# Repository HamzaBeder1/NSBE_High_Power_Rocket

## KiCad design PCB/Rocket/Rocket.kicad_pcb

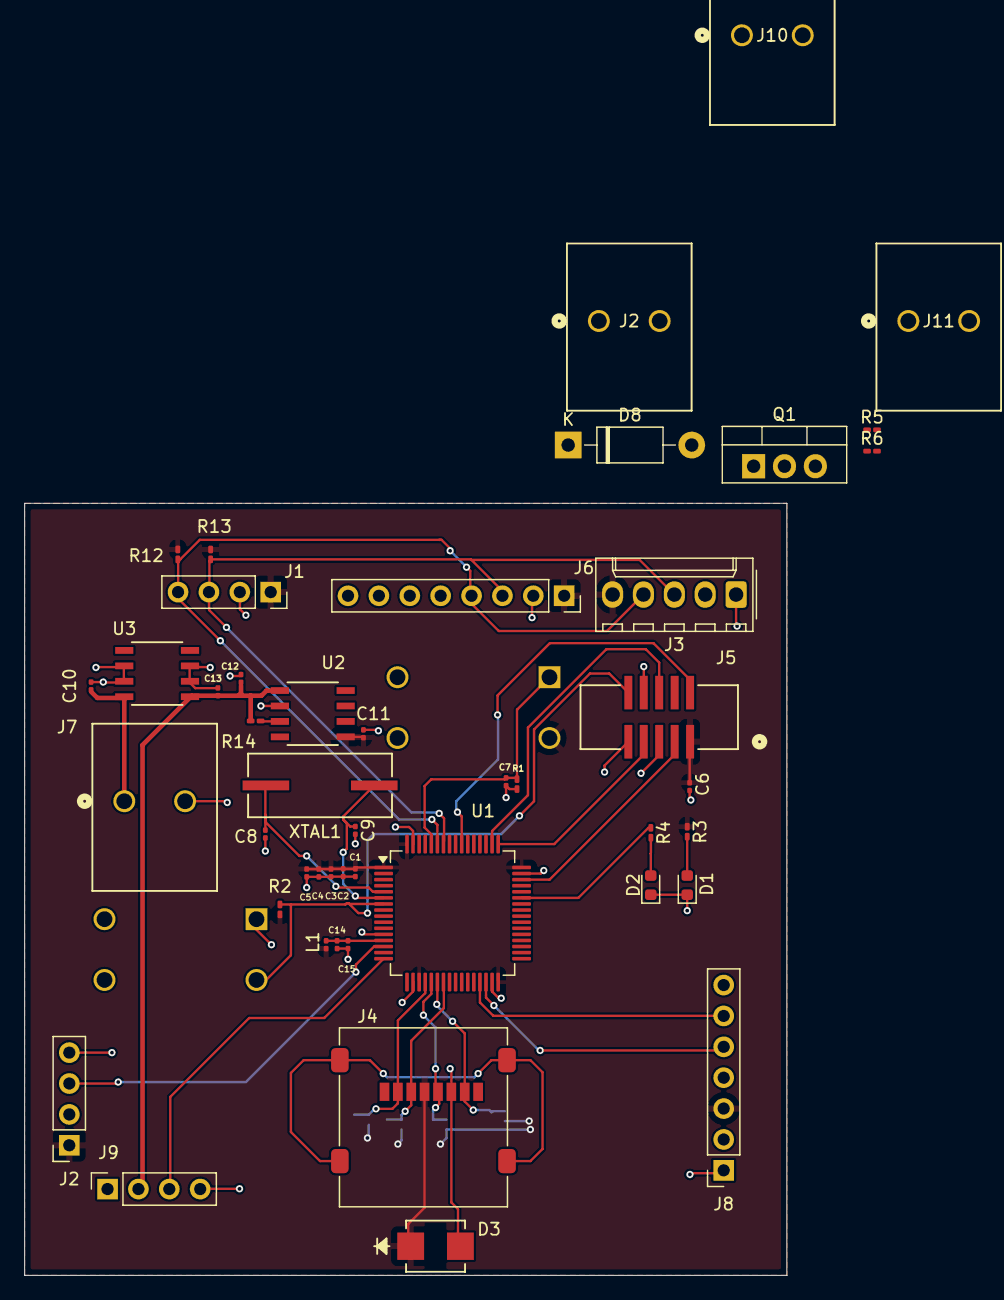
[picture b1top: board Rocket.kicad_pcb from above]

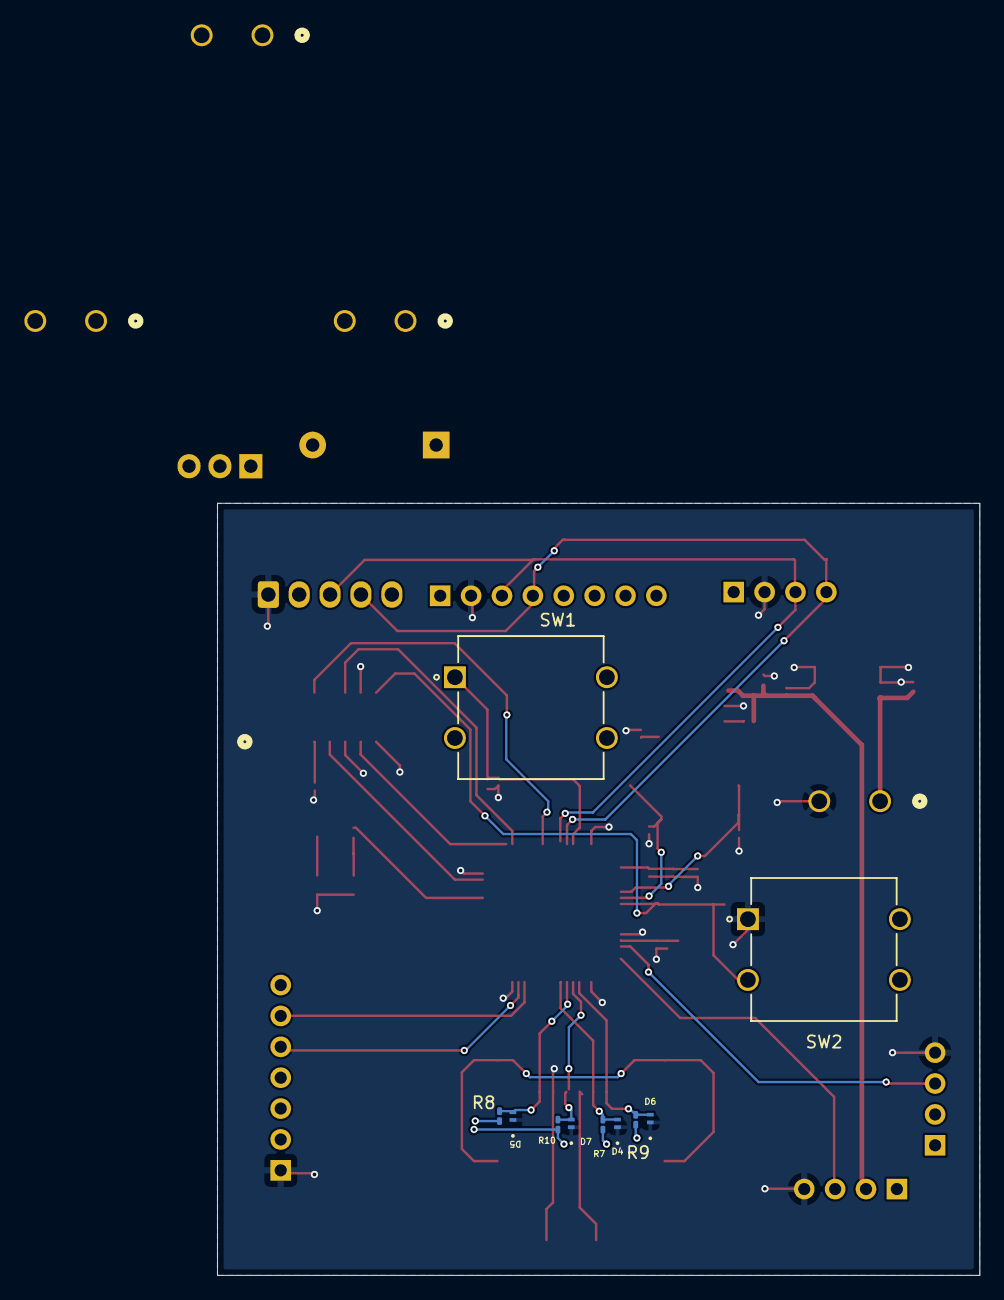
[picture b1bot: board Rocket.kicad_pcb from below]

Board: 2 copper layers, 62.7 x 63.5 mm, 56 parts (10 on the bottom side), 29 nets.

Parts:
C1, C2, C3, C4, C5, C6, C7, C13: 100nF; C_0201_0603Metric
C8, C9: 18pF; C_0201_0603Metric
C10: 0.33uf; C_0201_0603Metric
C11, C12, C14: 1uF; C_0201_0603Metric
C15: 10uf; C_0201_0603Metric
D1, D2: LED; LED_0603_1608Metric
D3: SMLVT3V3; SMB_STM
D4, D5, D6, D7: PESD5V0S1UL_315; DFN1006-2_SOD882_NEX
D8: 1N4001; D_DO-41_SOD81_P10.16mm_Horizontal
J1, J2, J9: PinSocket_1x04_P2.54mm_Vertical
J2#2, J7, J10, J11: 1987724; CONN_1987724_PXC
J3: Molex_KK-254_AE-6410-05A_1x05_P2.54mm_Vertical
J4: Micro_SD_Card; microSD_HC_Molex_47219-2001
J5: Conn_ARM_JTAG_SWD_10; CONN10_3221-10-0300-00_CNC
J6: PinSocket_1x08_P2.54mm_Vertical
J8: PinSocket_1x07_P2.54mm_Vertical
L1: 3.3uh; L_0201_0603Metric
Q1: IRLZ44N; TO-220-3_Vertical
R1, R2, R5, R7, R8, R9, R10, R14: 10k; R_0201_0603Metric_Pad0.64x0.40mm_HandSolder
R3, R4, R6: 220; R_0201_0603Metric_Pad0.64x0.40mm_HandSolder
R12, R13: 4.7K; R_0201_0603Metric_Pad0.64x0.40mm_HandSolder
SW1, SW2: COM-10302
U1: STM32L476RGTx; LQFP-64_10x10mm_P0.5mm
U2: MIC5365-3.3YC5-TR; SOIC8_ONS
U3: MC78L05ACDR2G; SOIC8_ONS
XTAL1: ABLS-8.000MHZ-K4T; CRYSTAL_ABLS-8.000MHZ-K4T_ABR

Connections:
+3.3V: C1.1, C2.1, C3.1, C4.1, C5.1, C6.1, C11.2, D3.1, J1.1, J2.1, J3.5, J4.4 (VDD), J5.1 (VTref), J6.1, J8.3, L1.1, R2.1, R3.1, R7.2, R8.2, R9.2, R10.2, R12.2, R13.2, SW1.3, U1.1 (VBAT), U1.19 (VDD), U1.32 (VDD), U1.48 (VDDUSB), U1.64 (VDD), U2.5 (VOUT)
+3.3VA: C14.1, C15.1, L1.2, U1.13 (VDDA)
+5V: C12.1, C13.2, J2#2.1, J9.2, R14.2, U2.1 (VIN), U3.1 (VOUT)
+VDC: C10.1, D8.1 (K), J7.1, U3.8 (VIN)
/BOOT0: C7.1, R1.2, SW1.1, U1.60 (BOOT0)
/CS: D6.2, J4.2 (DAT3/CD), R9.1, U1.20 (PA4)
/GPIO_LED: R4.1, U1.43 (PA10)
/MISO: D5.2, J4.7 (DAT0), R8.1, U1.22 (PA6)
/MOSI: D4.2, J4.3 (CMD), R7.1, U1.23 (PA7)
/NRST: J5.10 (~RESET), R2.2, SW2.3, U1.7 (NRST)
/OSC_IN: C8.1, U1.5 (PH0), XTAL1.1
/OSC_OUT: C9.1, U1.6 (PH1), XTAL1.2
/PRESSURE_OUT: J9.3, U1.16 (PA2)
/PWM: J2.3, J11.1, U1.14 (PA0)
/RX: J8.5, U1.30 (PB11)
/SCK: D7.2, J4.5 (CLK), R10.1, U1.21 (PA5)
/SCL: J1.3, J3.3, J6.3, R12.1, U1.58 (PB6)
/SDA: J1.4, J3.4, J6.4, R13.1, U1.59 (PB7)
/TCK: J5.4 (SWCLK/TCK), U1.49 (PA14)
/TDI: J5.8 (NC/TDI), U1.50 (PA15)
/TDO: J5.6 (SWO/TDO), U1.55 (PB3)
/TMS: J5.2 (SWDIO/TMS), U1.46 (PA13)
/TX: J8.6, U1.29 (PB10)
GND: C1.2, C2.2, C3.2, C4.2, C5.2, C6.2, C7.2, C8.2, C9.2, C10.2, C11.1, C12.2, C13.1, C14.2, C15.2, D1.1 (K), D2.1 (K), D3.2, D4.1, D5.1, D6.1, D7.1, J1.2, J2.4, J2#2.2, J3.1, J4.6 (VSS), J5.3 (GND), J5.5 (GND), J5.9 (GNDDetect), J6.2, J7.2, J8.1, J9.4, Q1.3 (S), R1.1, R5.1, SW2.1, U1.12 (VSSA), U1.18 (VSS), U1.31 (VSS), U1.47 (VSS), U1.63 (VSS), U2.2 (GND), U3.2 (GND), U3.3 (GND), U3.6 (GND), U3.7 (GND)
unnamed: D1.2 (A), R3.2
unnamed: D2.2 (A), R4.2
unnamed: D8.2 (A), J10.1, Q1.2 (D)
unnamed: Q1.1 (G), R5.2, R6.1
unnamed: R14.1, U2.3 (EN)

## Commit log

2024-11-22 First firmware commit.
2024-11-24 Changed configuration files.
2024-11-27 Updated initialization.
2024-11-27 Added I2C initialization code.
2024-11-28 Added DMA code for I2C.
2024-12-01 Updated DMA initialization code.
    DMA works now, but it only allows one send/receive transaction unless I
    use debug mode.
2024-12-03 Updated I2C and DMA code.
2024-12-03 Fixed issue with i2C and DMA. Just an issue with the order I called the initialization functions.
2024-12-03 Added FSM for I2C transmission.
2024-12-24 Added read and write register functions.
2024-12-24 Added firmware for MPU6050. Currently, all three axes are returning 0 acceleration.
2024-12-24 Updated MPU6050 firmware.
    The module returns non-zero values, but they are incorrect.
2024-12-24 Added BMP180 firmware for calculating temperature.
2024-12-24 Added firmware for calculating pressure using BMP180.
2024-12-24 Added firmware for DS3231.
2024-12-28 Added firmware for calculating velocity and acceleration from MPU6050.
2024-12-28 Added firmware for getting altitutde, velocity, and acceleration from BMP180.
2024-12-30 Added firmware for calculating velocity and acceleration from BMP180.
    Working on fixing output from MPU6050. Currently, acceleration values
    are incorrect.
2024-12-31 Added firmware for SD card.
2025-01-01 Added functions for reading/writing multiple blocks from/to the SD card.
2025-01-07 Added firmware for reading and writing from/to file system.
2025-01-07 Updated SD card firmware.
2025-01-07 Finished firmware for SD card and its file system.
2025-01-14 First PCB commit.
2025-01-17 Added initialization code for neom9n.
2025-01-17 Added firmware for getting PVT data from NEOM9N.
2025-01-20 Added VDDA filtering and LED indicators.
2025-01-22 Added ESD protection for SD card and pull up resistors.
2025-02-01 Updated layout.
2025-02-06 Fixing DRC errors.
2025-02-06 Removed silkscreen errors.
2025-02-06 Removed all DRC errors.
2025-02-06 Adjusted trace widths.
2025-02-06 Fixed I2C traces.
2025-02-06 Fixed SPI connections.
2025-02-06 Fixed UART traces.
2025-02-08 Fixed TVS diode and C6 connection.
2025-02-08 Updated footprints for regulators and silkscreen.
2025-02-22 Changed bmp180.c
2025-03-23 Updating to use arduino instead of STM32
2025-03-27 Updated PCB

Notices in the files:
parts and their libraries:
Copyright 2016 Accelerated Designs. All rights reserved.
